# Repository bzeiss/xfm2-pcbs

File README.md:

# PCB(s) for the XFM2/XVA1 Project

This site contains some stuff I have built for the excellent FPGA XFM2/XVA FPGA DIY synths by futur3soundz/René Ceballos. You can find them here: https://www.futur3soundz.com.

I tinker with electronics, release stuff when I feel like it and I make it public when it's maybe not perfect. I'm not an electronics expert, so I may not always know what I'm doing. I learn the necessary electronics as I use it. Use at your own risk.

Feedback is always very welcome 😄 Feel free to ask question in the [discussions](https://github.com/bzeiss/xfm2-pcbs/discussions).

***

The main content of this site (descriptions, documentations) can be found **[in the Wiki](https://github.com/bzeiss/xfm2-pcbs/wiki)**.

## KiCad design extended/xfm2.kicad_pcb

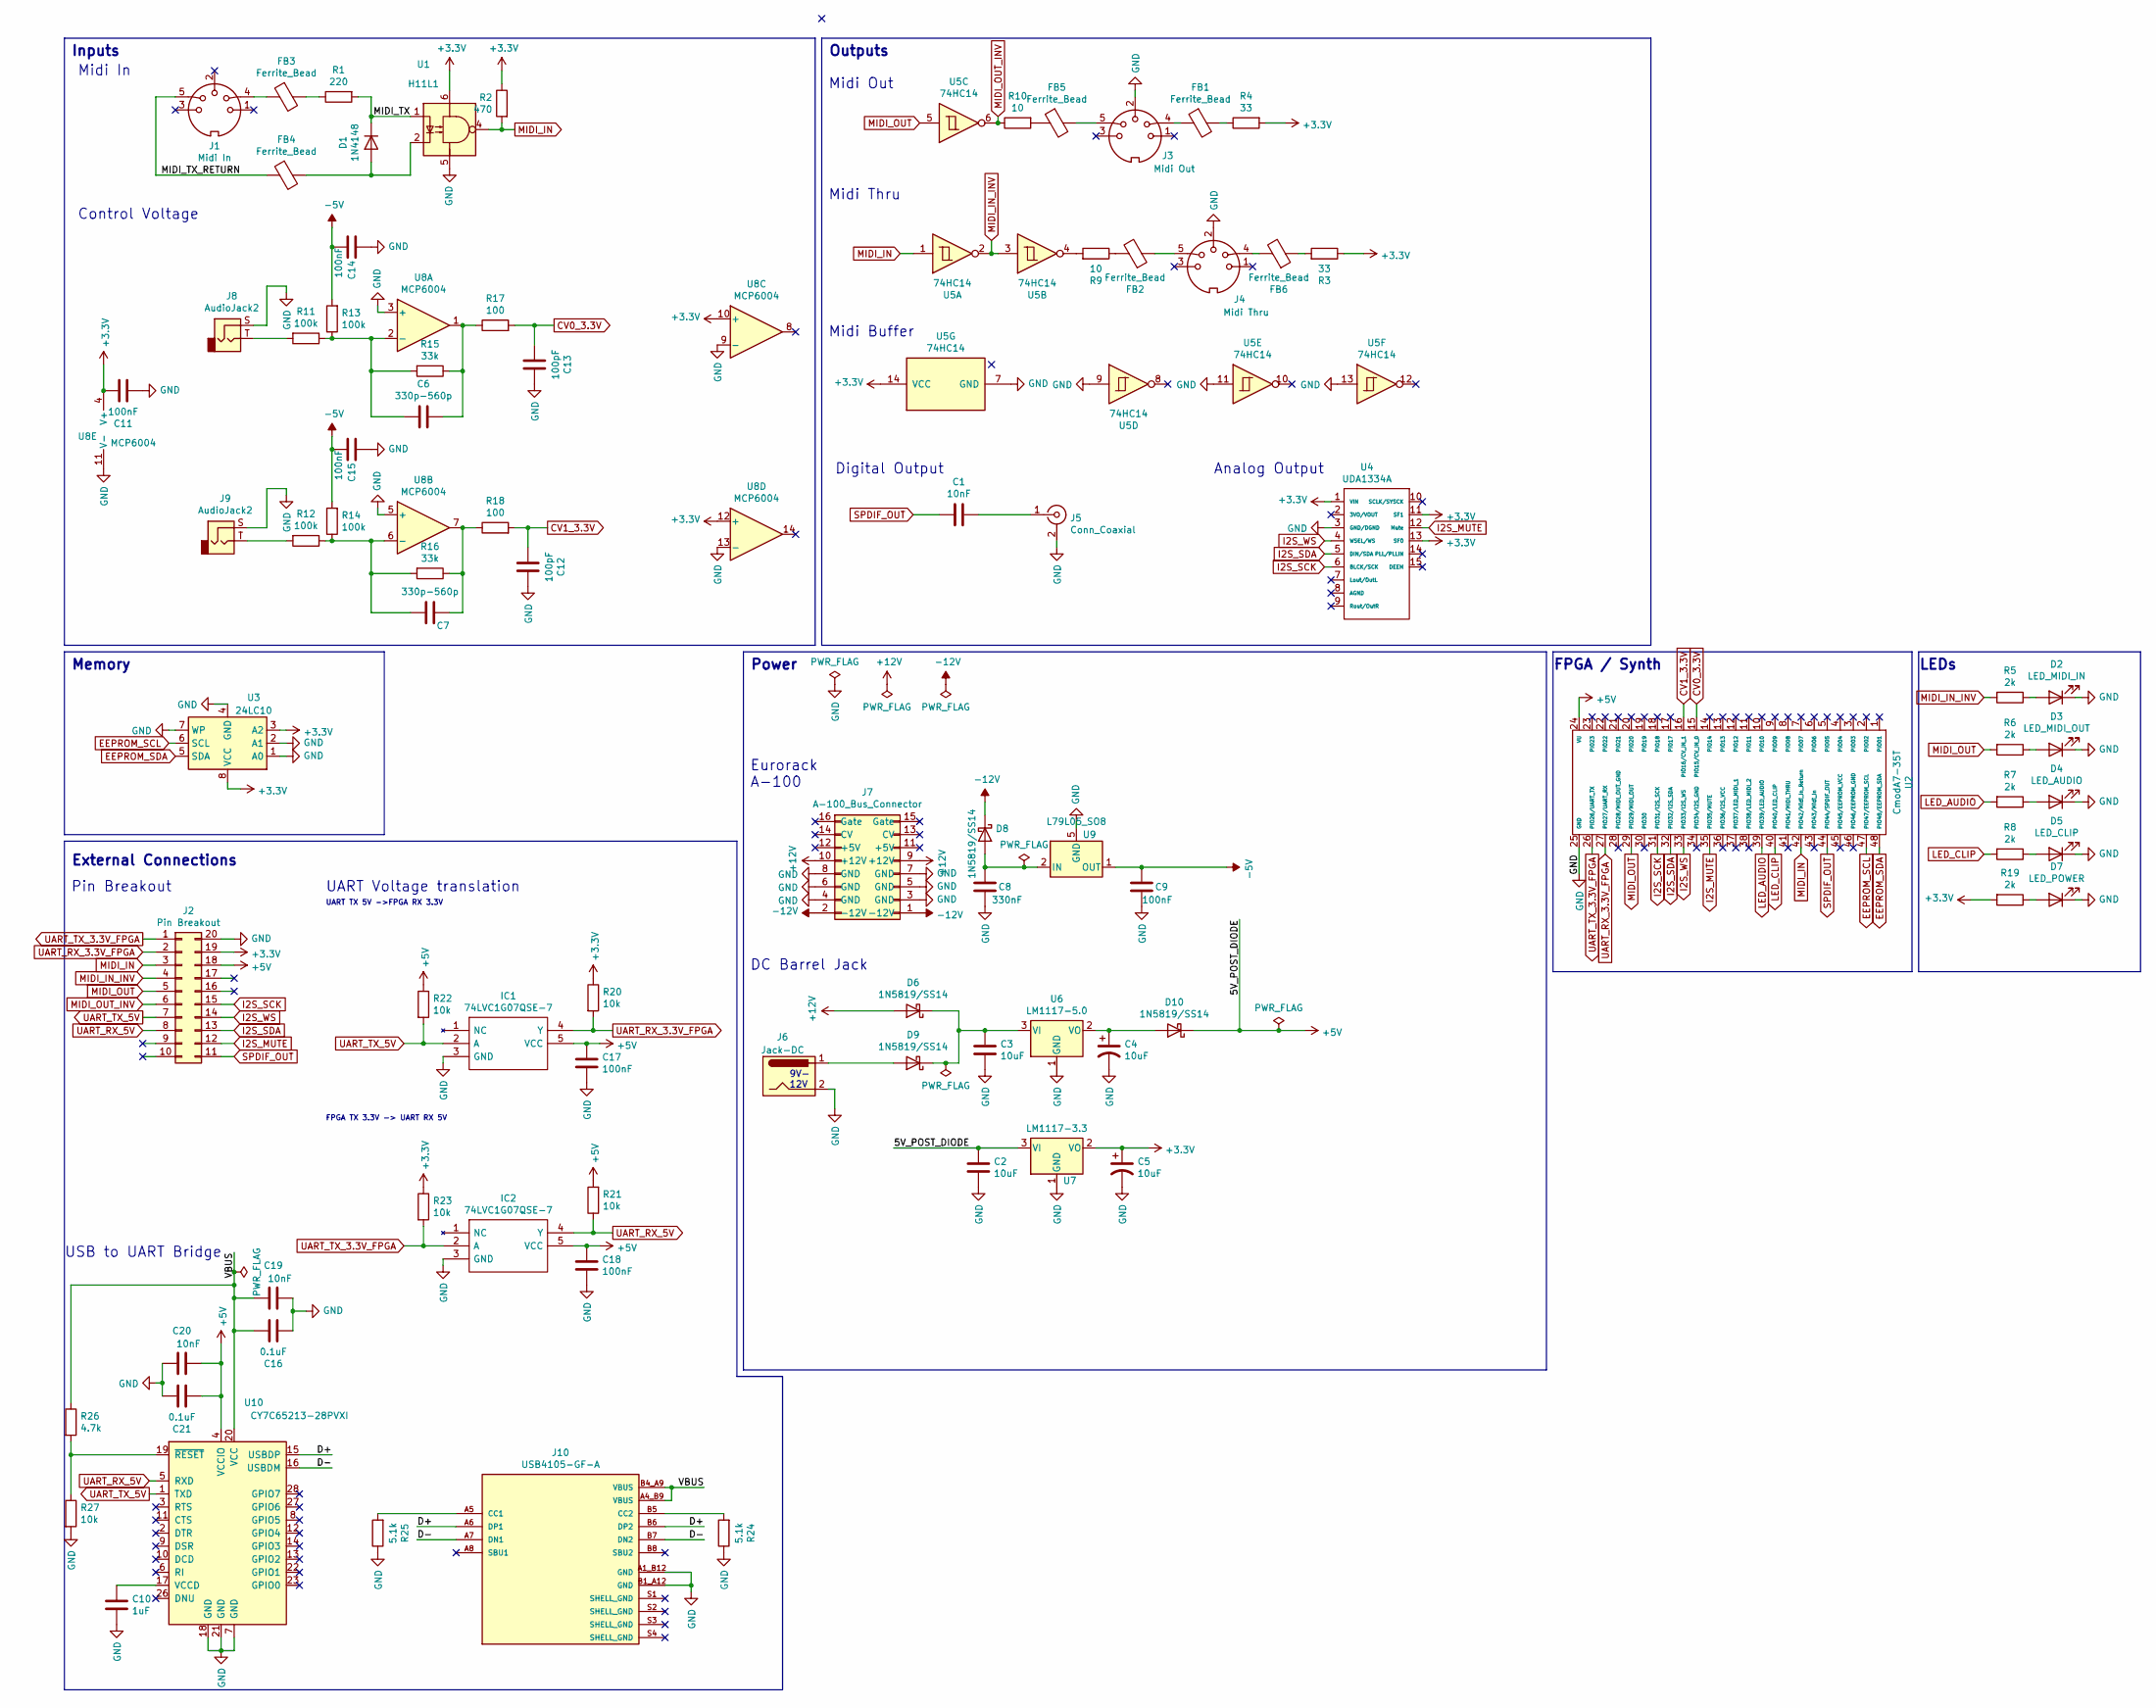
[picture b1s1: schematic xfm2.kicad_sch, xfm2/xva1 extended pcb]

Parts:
C1, C19, C20: 10nF; C_0805_2012Metric_Pad1.18x1.45mm_HandSolder; LCSC C1710
C2, C3: 10uF; C_0805_2012Metric_Pad1.18x1.45mm_HandSolder; LCSC C15850
C4, C5: 10uF; CP_EIA-3216-18_Kemet-A_Pad1.58x1.35mm_HandSolder; LCSC C7171
C6, C7: 330p-560p; C_0805_2012Metric_Pad1.18x1.45mm_HandSolder; LCSC C51207
C8: 330nF; C_0805_2012Metric_Pad1.18x1.45mm_HandSolder; LCSC C1740
C9, C11, C14, C15, C17, C18: 100nF; C_0805_2012Metric_Pad1.18x1.45mm_HandSolder; LCSC C49678
C10: 1uF; C_0805_2012Metric_Pad1.18x1.45mm_HandSolder; LCSC C28323
C12, C13: 100pF; C_0805_2012Metric_Pad1.18x1.45mm_HandSolder; LCSC C1790
C16, C21: 0.1uF; C_0805_2012Metric_Pad1.18x1.45mm_HandSolder; LCSC C49678
D1: 1N4148; D_SOD-323_HandSoldering; LCSC C2128
D2: LED_MIDI_IN; LED_0805_2012Metric_Pad1.15x1.40mm_HandSolder; LCSC C2293
D3: LED_MIDI_OUT; LED_0805_2012Metric_Pad1.15x1.40mm_HandSolder; LCSC C2296
D4: LED_AUDIO; LED_0805_2012Metric_Pad1.15x1.40mm_HandSolder
D5: LED_CLIP; LED_0805_2012Metric_Pad1.15x1.40mm_HandSolder; LCSC C434431
D6, D8, D9, D10: 1N5819/SS14; D_SMA-SMB_Universal_Handsoldering; LCSC C2480
D7: LED_POWER; LED_0805_2012Metric_Pad1.15x1.40mm_HandSolder; LCSC C2297
FB1, FB2, FB3, FB4, FB5, FB6: Ferrite_Bead; C_0805_2012Metric_Pad1.18x1.45mm_HandSolder; LCSC C76810
IC1, IC2: 74LVC1G07QSE-7; SOT25; Mouser Part Number 621-74LVC1G07QSE-7
J1: Midi In; din-5
J2: Pin Breakout; PinHeader_2x10_P2.54mm_Vertical
J3: Midi Out; din-5
J4: Midi Thru; din-5
J5: Conn_Coaxial; KLPX0848A2Y
J6: Jack-DC; BarrelJack_Wuerth_6941xx301002
J7: A-100_Bus_Connector; PinHeader_2x08_P2.54mm_Vertical
J8, J9: AudioJack2; Jack_6.35mm_Neutrik_NMJ6HFD2_Horizontal-ST-only
J10: USB4105-GF-A; GCT_USB4105-GF-A; PARTREV A3
R1: 220; R_0805_2012Metric_Pad1.20x1.40mm_HandSolder; LCSC C17557
R2: 470; R_0805_2012Metric_Pad1.20x1.40mm_HandSolder; LCSC C17710
R3, R4: 33; R_0805_2012Metric_Pad1.20x1.40mm_HandSolder; LCSC C17634
R5, R6, R7, R8, R19: 2k; R_0805_2012Metric_Pad1.20x1.40mm_HandSolder; LCSC C17604
R9, R10: 10; R_0805_2012Metric_Pad1.20x1.40mm_HandSolder; LCSC C17415
R11, R12, R13, R14: 100k; R_0805_2012Metric_Pad1.20x1.40mm_HandSolder; LCSC C149504
R15, R16: 33k; R_0805_2012Metric_Pad1.20x1.40mm_HandSolder; LCSC C17633
R17, R18: 100; R_0805_2012Metric_Pad1.20x1.40mm_HandSolder; LCSC C17408
R20, R21, R22, R23, R27: 10k; R_0805_2012Metric_Pad1.20x1.40mm_HandSolder; LCSC C17414
R24, R25: 5.1k; R_0805_2012Metric_Pad1.20x1.40mm_HandSolder; LCSC C27834
R26: 4.7k; R_0805_2012Metric_Pad1.20x1.40mm_HandSolder; LCSC C17673
U1: H11L1; SMDIP-6_W9.53mm_Clearance8mm; LCSC C20082
U2: CmodA7-35T; DIP-48_W15.24mm_LongPads
U3: 24LC10; SOIC-8_5.275x5.275mm_P1.27mm; LCSC C1348777
U4: UDA1334A; Adafruit_UDA1334A_Breakout
U5: 74HC14; SO-14_3.9x8.65mm_P1.27mm; LCSC C6820
U6: LM1117-5.0; SOT-223-3_TabPin2; LCSC C126028
U7: LM1117-3.3; SOT-223-3_TabPin2; LCSC C126027
U8: MCP6004; SO-14_5.3x10.2mm_P1.27mm; LCSC C7378
U9: L79L05_SO8; SOIC-8_3.9x4.9mm_P1.27mm; LCSC C2802525
U10: CY7C65213-28PVXI; SSOP-28_5.3x10.2mm_P0.65mm; LCSC C134181

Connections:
+3V3: C5.1, C11.1, J2.19, R2.1, R3.1, R4.2, R19.2, R20.1, R23.1, U1.6, U3.3 (A2), U3.8 (VCC), U4.1 (VIN), U4.11 (SF1), U4.13 (SF0), U5.14 (VCC), U7.2 (VO), U8.4 (V+), U8.10 (+), U8.12 (+)
+5V: C2.1, C17.1, C18.1, C20.2, C21.2, D10.1 (K), IC1.5 (VCC), IC2.5 (VCC), J2.18, R21.2, R22.1, U2.24 (VU), U7.3 (VI), U10.4 (VCCIO)
+12V: D6.2 (A), J7.9 (+12V), J7.10 (+12V)
-5V: C9.1, C14.2, C15.2, R13.2, R14.2, U9.1 (OUT)
-12V: D8.1 (K), J7.1 (-12V), J7.2 (-12V)
/D+: J10.A6 (DP1), J10.B6 (DP2), U10.15 (USBDP)
/D-: J10.A7 (DN1), J10.B7 (DN2), U10.16 (USBDM)
/MIDI_TX: D1.1 (K), R1.2, U1.1
/MIDI_TX_RETURN: FB4.1, J1.5
/VBUS: C16.1, C19.1, J10.A4_B9 (VBUS), J10.B4_A9 (VBUS), R26.1, U10.20 (VCC)
CV0_3.3V: C13.2, R17.2, U2.15 (PIO15/CV_IN_0)
CV1_3.3V: C12.2, R18.2, U2.16 (PIO16/CV_IN_1)
EEPROM_SCL: U2.47 (PIO47/EEPROM_SCL), U3.6 (SCL)
EEPROM_SDA: U2.48 (PIO48/EEPROM_SDA), U3.5 (SDA)
GND: C2.2, C3.2, C4.2, C5.2, C8.2, C9.2, C10.2, C11.2, C12.1, C13.1, C14.1, C15.1, C16.2, C17.2, C18.2, C19.2, C20.1, C21.1, D2.1 (K), D3.1 (K), D4.1 (K), D5.1 (K), D7.1 (K), IC1.3 (GND), IC2.3 (GND), J2.20, J3.2, J4.2, J5.2 (Ext), J6.2, J7.3 (GND), J7.4 (GND), J7.5 (GND), J7.6 (GND), J7.7 (GND), J7.8 (GND), J8.S, J9.S, J10.A1_B12 (GND), J10.B1_A12 (GND), R24.1, R25.1, R27.2, U1.5, U2.25 (GND), U3.1 (A0), U3.2 (A1), U3.4 (GND), U3.7 (WP), U4.3 (GND/DGND), U5.7 (GND), U5.9, U5.11, U5.13, U6.1 (GND), U7.1 (GND), U8.3 (+), U8.5 (+), U8.9 (-), U8.11 (V-), U8.13 (-), U9.5 (GND), U10.7 (GND), U10.18 (GND), U10.21 (GND)
I2S_MUTE: J2.12, U2.35 (PIO35/MUTE), U4.12 (Mute)
I2S_SCK: J2.15, U2.31 (PIO31/I2S_SCK), U4.6 (BLCK/SCK)
I2S_SDA: J2.13, U2.32 (PIO32/I2S_SDA), U4.5 (DIN/SDA)
I2S_WS: J2.14, U2.33 (PIO33/I2S_WS), U4.4 (WSEL/WS)
LED_AUDIO: R7.2, U2.39 (PIO39/LED_AUDIO)
LED_CLIP: R8.2, U2.40 (PIO40/LED_CLIP)
MIDI_IN: J2.3, R2.2, U1.4, U2.42 (PIO42/Midi_In_Return), U5.1
MIDI_IN_INV: J2.4, R5.2, U5.2, U5.3
MIDI_OUT: J2.5, R6.2, U2.29 (PIO29/MIDI_OUT), U5.5
MIDI_OUT_INV: J2.6, R10.1, U5.6
unnamed: C1.1, J5.1 (In)
unnamed: C3.1, D6.1 (K), D9.1 (K), U6.3 (VI)
unnamed: C4.1, D10.2 (A), U6.2 (VO)
unnamed: C6.1, R15.1, R17.1, U8.1
unnamed: C6.2, R11.1, R13.1, R15.2, U8.2 (-)
unnamed: C7.1, R16.1, R18.1, U8.7
unnamed: C7.2, R12.1, R14.1, R16.2, U8.6 (-)
unnamed: C8.1, D8.2 (A), U9.2 (IN), U9.3 (IN), U9.6 (IN), U9.7 (IN)
unnamed: C10.1, U10.17 (VCCD)
unnamed: D1.2 (A), FB4.2, U1.2
unnamed: D2.2 (A), R5.1
unnamed: D3.2 (A), R6.1
unnamed: D4.2 (A), R7.1
unnamed: D5.2 (A), R8.1
unnamed: D7.2 (A), R19.1
unnamed: D9.2 (A), J6.1
unnamed: FB1.1, J3.4
unnamed: FB1.2, R4.1
unnamed: FB2.1, J4.5
unnamed: FB2.2, R9.1
unnamed: FB3.1, J1.4
unnamed: FB3.2, R1.1
unnamed: FB5.1, R10.2
unnamed: FB5.2, J3.5
unnamed: FB6.1, R3.2
unnamed: FB6.2, J4.4
unnamed: J8.T, R11.2
unnamed: J9.T, R12.2
unnamed: J10.A5 (CC1), R25.2
unnamed: J10.B5 (CC2), R24.2
unnamed: R9.2, U5.4
unnamed: R26.2, R27.1, U10.19 (~RESET)
SPDIF_OUT: C1.2, J2.11, U2.44 (PIO44/SPDIF_OUT)
UART_RX_3.3V_FPGA: IC1.4 (Y), J2.2, R20.2, U2.27 (PIO27/UART_RX)
UART_RX_5V: IC2.4 (Y), J2.8, R21.1, U10.5 (RXD)
UART_TX_3.3V_FPGA: IC2.2 (A), J2.1, R23.2, U2.26 (PIO26/UART_TX)
UART_TX_5V: IC1.2 (A), J2.7, R22.2, U10.1 (TXD)

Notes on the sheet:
Inputs
FPGA / Synth
DC Barrel Jack
External Connections
Outputs
Eurorack A-100
UART TX 5V ->FPGA RX 3.3V
Midi Out
9V- 12V
Digital Output
Control Voltage
Midi Thru
Power
LEDs
Pin Breakout
Midi Buffer
USB to UART Bridge
Memory
FPGA TX 3.3V -> UART RX 5V
Midi In
Analog Output
UART Voltage translation

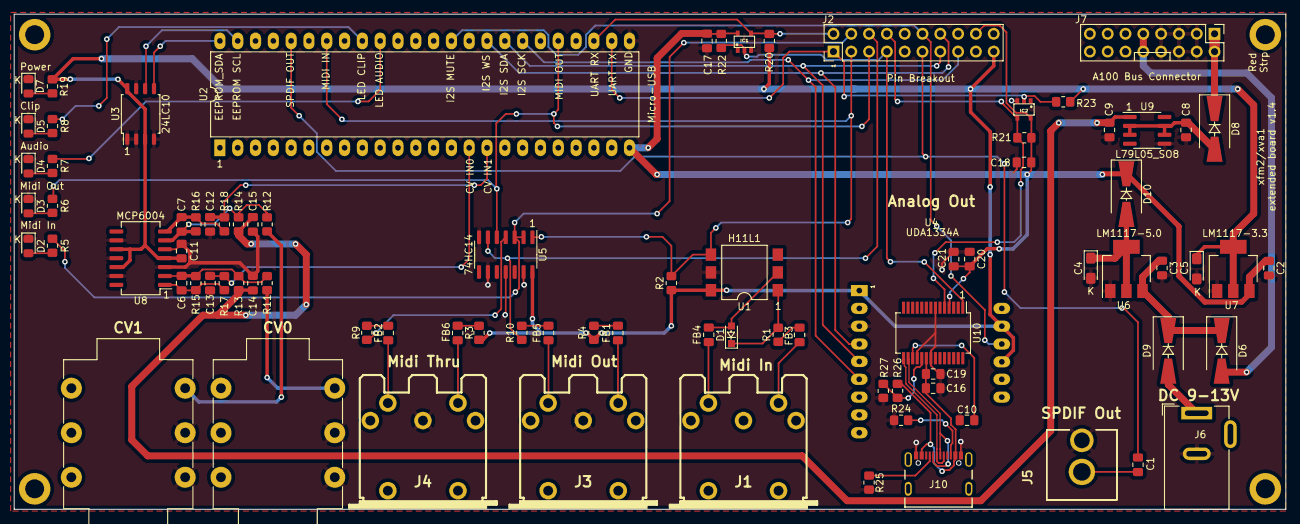
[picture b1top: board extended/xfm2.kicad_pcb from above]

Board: 2 copper layers, 181.4 x 70.6 mm, 86 parts (0 on the bottom side), 62 nets.

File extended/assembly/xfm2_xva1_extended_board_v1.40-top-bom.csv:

Comment;Designator;Footprint;LCSC Part Number
10nF;C1,C19,C20;Capacitor_SMD:C_0805_2012Metric_Pad1.18x1.45mm_HandSolder;C1710
1uF;C10;Capacitor_SMD:C_0805_2012Metric_Pad1.18x1.45mm_HandSolder;C28323
100pF;C12,C13;Capacitor_SMD:C_0805_2012Metric_Pad1.18x1.45mm_HandSolder;C1790
0.1uF;C16,C21;Capacitor_SMD:C_0805_2012Metric_Pad1.18x1.45mm_HandSolder;C49678
10uF;C2,C3;Capacitor_SMD:C_0805_2012Metric_Pad1.18x1.45mm_HandSolder;C15850
10uF;C4,C5;Capacitor_Tantalum_SMD:CP_EIA-3216-18_Kemet-A_Pad1.58x1.35mm_HandSolder;C7171
330p-560p;C6,C7;Capacitor_SMD:C_0805_2012Metric_Pad1.18x1.45mm_HandSolder;C51207
330nF;C8;Capacitor_SMD:C_0805_2012Metric_Pad1.18x1.45mm_HandSolder;C1740
100nF;C9,C11,C14,C15,C17,C18;Capacitor_SMD:C_0805_2012Metric_Pad1.18x1.45mm_HandSolder;C49678
1N4148;D1;Diode_SMD:D_SOD-323_HandSoldering;C2128
LED_MIDI_IN;D2;LED_SMD:LED_0805_2012Metric_Pad1.15x1.40mm_HandSolder;C2293
LED_MIDI_OUT;D3;LED_SMD:LED_0805_2012Metric_Pad1.15x1.40mm_HandSolder;C2296
LED_CLIP;D5;LED_SMD:LED_0805_2012Metric_Pad1.15x1.40mm_HandSolder;C434431
1N5819/SS14;D6,D8,D9,D10;Diode_SMD:D_SMA-SMB_Universal_Handsoldering;C2480
LED_POWER;D7;LED_SMD:LED_0805_2012Metric_Pad1.15x1.40mm_HandSolder;C2297
Ferrite_Bead;FB1,FB2,FB3,FB4,FB5,FB6;Capacitor_SMD:C_0805_2012Metric_Pad1.18x1.45mm_HandSolder;C76810
74LVC1G07QSE-7;IC1,IC2;greatscott:SOT25;C507244
220;R1;Resistor_SMD:R_0805_2012Metric_Pad1.20x1.40mm_HandSolder;C17557
100k;R11,R12,R13,R14;Resistor_SMD:R_0805_2012Metric_Pad1.20x1.40mm_HandSolder;C149504
33k;R15,R16;Resistor_SMD:R_0805_2012Metric_Pad1.20x1.40mm_HandSolder;C17633
100;R17,R18;Resistor_SMD:R_0805_2012Metric_Pad1.20x1.40mm_HandSolder;C17408
470;R2;Resistor_SMD:R_0805_2012Metric_Pad1.20x1.40mm_HandSolder;C17710
10k;R20,R21,R22,R23,R27;Resistor_SMD:R_0805_2012Metric_Pad1.20x1.40mm_HandSolder;C17414
5.1k;R24,R25;Resistor_SMD:R_0805_2012Metric_Pad1.20x1.40mm_HandSolder;C27834
4.7k;R26;Resistor_SMD:R_0805_2012Metric_Pad1.20x1.40mm_HandSolder;C17673
33;R3,R4;Resistor_SMD:R_0805_2012Metric_Pad1.20x1.40mm_HandSolder;C17634
2k;R5,R6,R7,R8,R19;Resistor_SMD:R_0805_2012Metric_Pad1.20x1.40mm_HandSolder;C17604
10;R9,R10;Resistor_SMD:R_0805_2012Metric_Pad1.20x1.40mm_HandSolder;C17415
H11L1;U1;Package_DIP:SMDIP-6_W9.53mm_Clearance8mm;C20082
CY7C65213-28PVXI;U10;Package_SO:SSOP-28_5.3x10.2mm_P0.65mm;C134181
24LC10;U3;Package_SO:SOIC-8_5.275x5.275mm_P1.27mm;C1348777
74HC14;U5;Package_SO:SO-14_3.9x8.65mm_P1.27mm;C6820
LM1117-5.0;U6;Package_TO_SOT_SMD:SOT-223-3_TabPin2;C126028
LM1117-3.3;U7;Package_TO_SOT_SMD:SOT-223-3_TabPin2;C126027
MCP6004;U8;Package_SO:SO-14_5.3x10.2mm_P1.27mm;C7378
L79L05_SO8;U9;Package_SO:SOIC-8_3.9x4.9mm_P1.27mm;C2802525
